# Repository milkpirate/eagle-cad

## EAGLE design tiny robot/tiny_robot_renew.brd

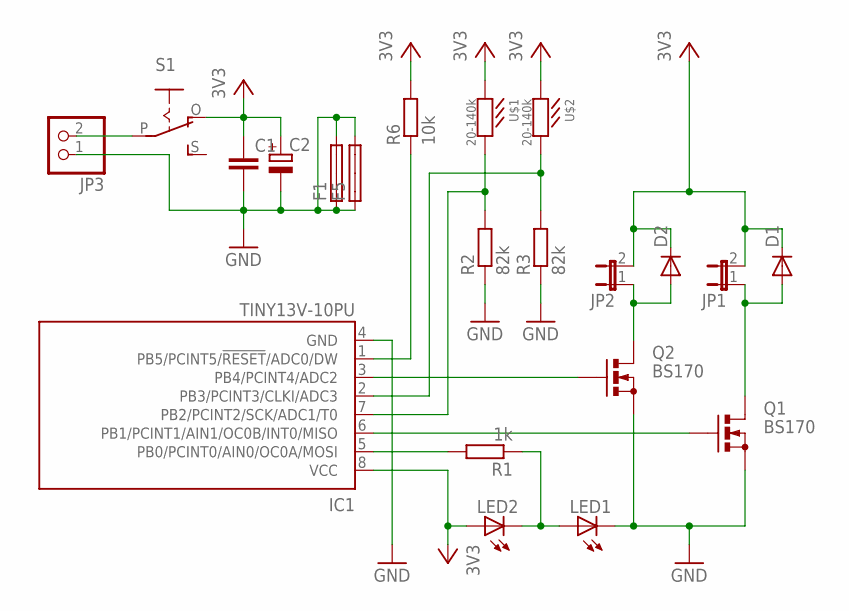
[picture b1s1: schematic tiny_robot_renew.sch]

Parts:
C1: C-EU025-025X050; C025-025X050
C2: CPOL-EUE2,5-6E; E2,5-6E
D1, D2: DIODE-D-2.5; D-2.5
F1: SHK20L
F5: SHK20Q
IC1: TINY13V-10PU; DIL08
JP1, JP2: JP1E; JP1
JP3: PINHD-1X2; 1X02
LED1, LED2: LED3MM
Q1, Q2: BS170; SOT54E
R1: 1k; 0204/7
R2, R3: 82k; 0207/2V
R6: 10k; 0204/7
S1: EG1218S; EG1218
U$1, U$2: 20-140k; LDR-906014

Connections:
GND: C1.2, C2.-, F1.1A, F1.2A, F5.1A, F5.2A, IC1.4 (GND), JP3.1, LED1.K (C), Q1.S, Q2.S, R2.1, R3.1
unnamed: IC1.3 (PB4/PCINT4/ADC2), Q2.G
unnamed: IC1.5 (PB0/PCINT0/AIN0/OC0A/MOSI), R1.2
unnamed: IC1.6 (PB1/PCINT1/AIN1/OC0B/INT0/MISO), Q1.G
unnamed: LED1.A, LED2.K (C), R1.1
unnamed: JP3.2, S1.P
unnamed: D2.A, JP2.1, Q2.D
unnamed: D1.A, JP1.1, Q1.D
unnamed: IC1.2 (PB3/PCINT3/CLKI/ADC3), R3.2, U$2.P$2
unnamed: IC1.7 (PB2/PCINT2/SCK/ADC1/T0), R2.2, U$1.P$2
RST: IC1.1 (PB5/PCINT5/!RESET!/ADC0/DW), R6.1
VCC: C1.1, C2.+, D1.C, D2.C, IC1.8 (VCC), JP1.2, JP2.2, LED2.A, R6.2, S1.O, U$1.P$1, U$2.P$1

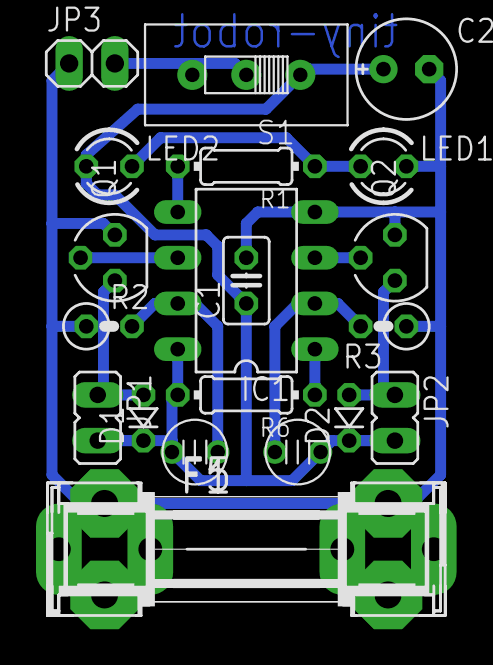
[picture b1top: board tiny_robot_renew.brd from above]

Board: 2 copper layers, 21 parts (0 on the bottom side), 12 nets.

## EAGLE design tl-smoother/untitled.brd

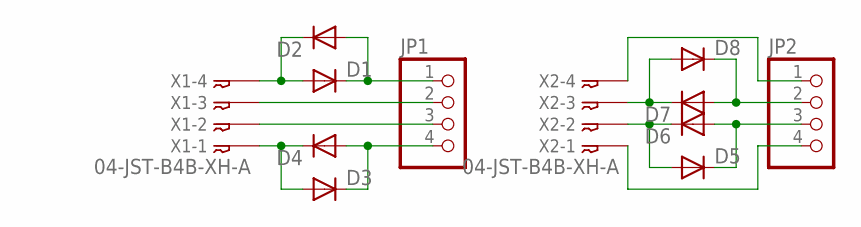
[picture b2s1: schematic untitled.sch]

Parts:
D1, D2, D3, D4: DIODE-SMB; SMB
D5, D6, D7, D8: DIODE-SMC; SMC
JP1, JP2: PINHD-1X4; 1X04
X1, X2: 04-JST-B4B-XH-A; B4B-XH

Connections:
unnamed: JP1.3, X1.P$2
unnamed: JP1.2, X1.P$3
unnamed: D1.C, D2.A, JP1.1
unnamed: D1.A, D2.C, X1.P$4
unnamed: D3.A, D4.C, X1.P$1
unnamed: D3.C, D4.A, JP1.4
unnamed: JP2.4, X2.P$1
unnamed: JP2.1, X2.P$4
unnamed: D7.A, D8.C, JP2.2
unnamed: D7.C, D8.A, X2.P$3
unnamed: D5.A, D6.C, X2.P$2
unnamed: D5.C, D6.A, JP2.3

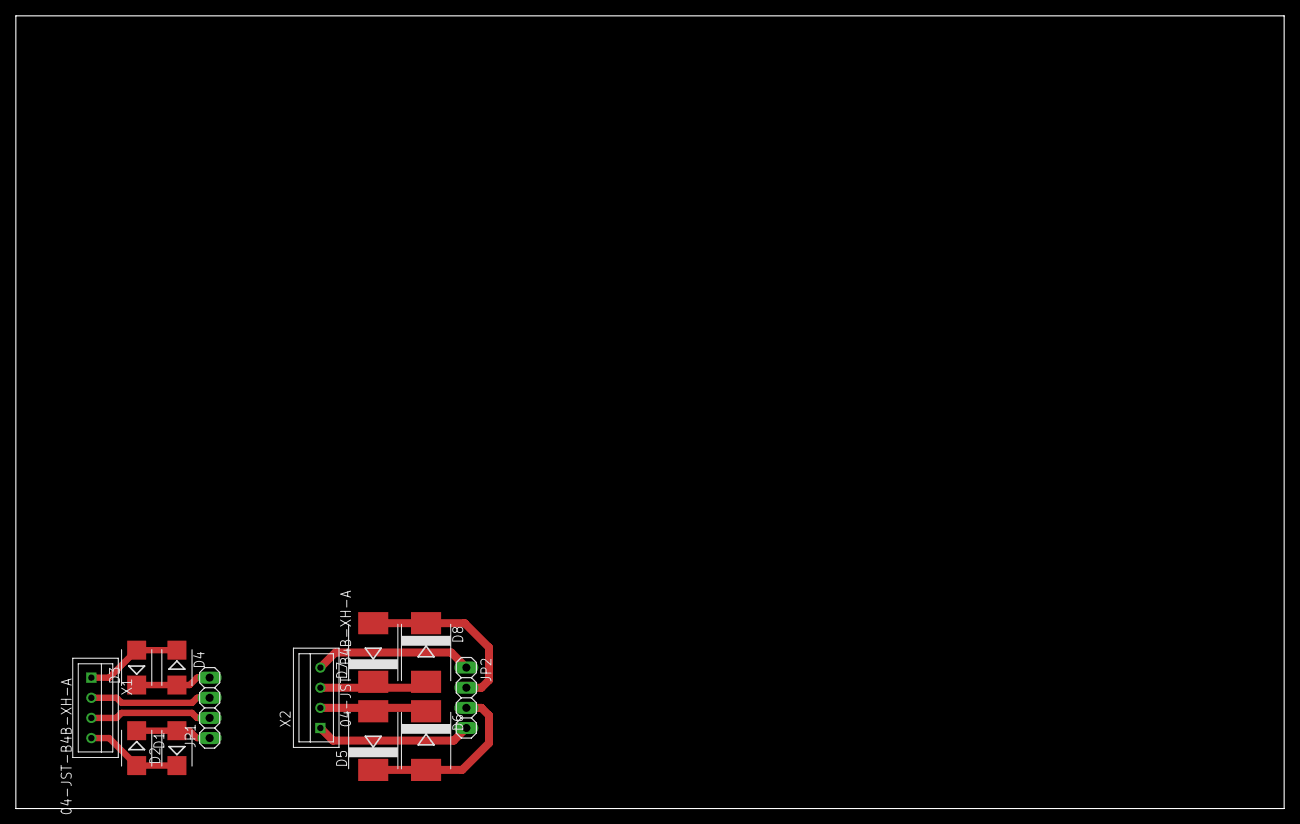
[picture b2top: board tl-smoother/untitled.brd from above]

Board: 2 copper layers, 160.0 x 100.0 mm, 12 parts (0 on the bottom side), 12 nets.

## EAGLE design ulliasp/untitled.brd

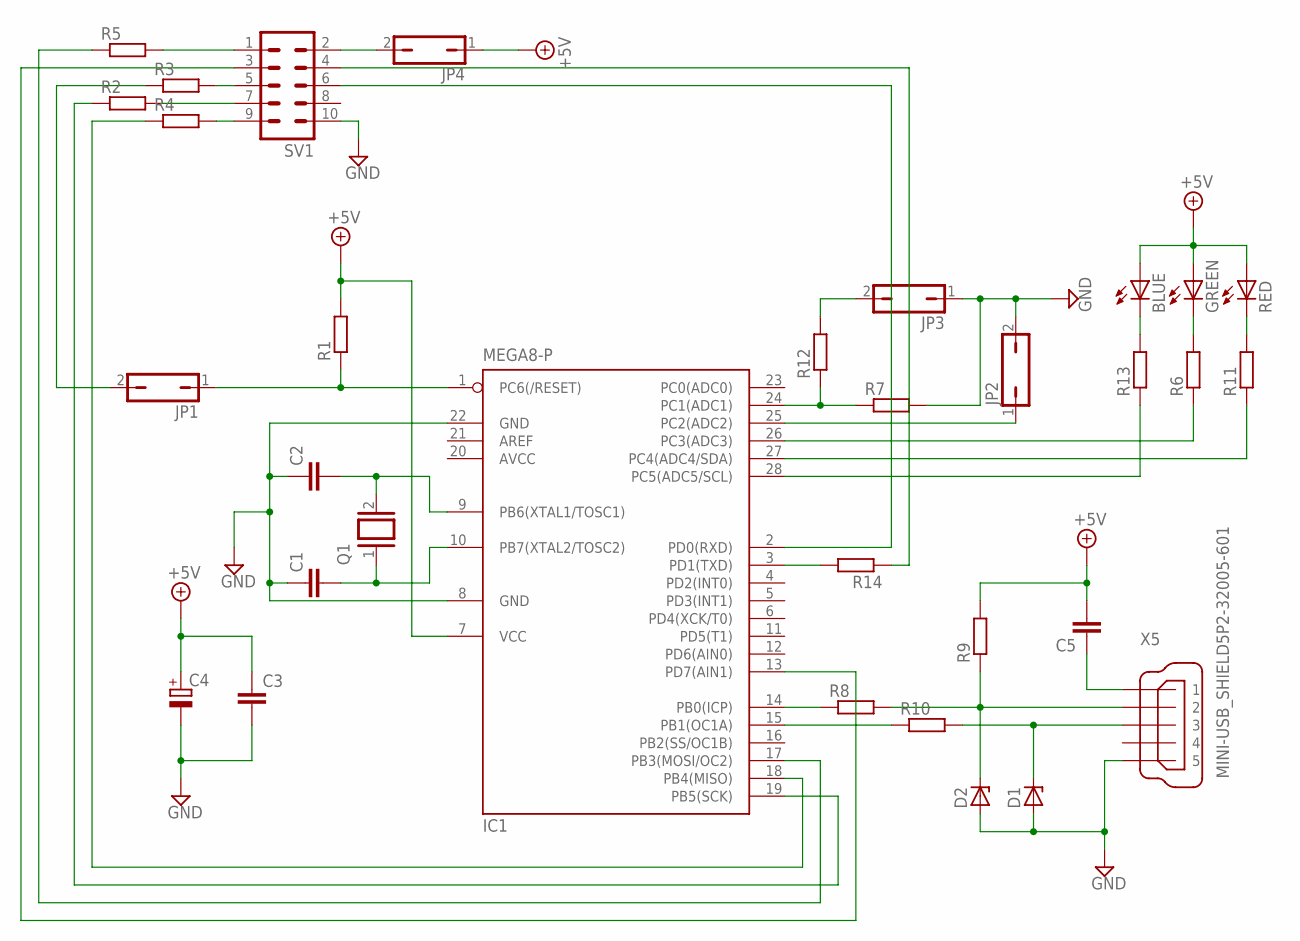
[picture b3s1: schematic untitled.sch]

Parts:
BLUE: LED5MM
C1, C2: C-EU025-025X050; C025-025X050
C3, C5: C-EU025_050-025X075; C025_050-025X075
C4: CPOL-EUE2.5-5; E2,5-5
D1: ZENER-DIODEZD-5; ZDIO-5
D2: ZENER-DIODEZD-2.5; ZDIO-2.5
GREEN: LED5MM
IC1: MEGA8-P; DIL28-3
JP1, JP2, JP3, JP4: JP1Q; JP1
Q1: XTAL/S; QS
R1, R2, R3, R4, R5, R8, R9, R10, R14: R-EU_0207/2V; 0207/2V
R6, R7, R11, R12, R13: R-EU_0204/5; 0204/5
RED: LED5MM
SV1: ML10
X5: MINI-USB_SHIELD5P2-32005-601; 32005-601

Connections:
+5V: BLUE.A, C3.1, C4.+, C5.2, GREEN.A, IC1.7 (VCC), JP4.1, R1.2, R9.2, RED.A
AVCC: IC1.20 (AVCC)
D+: D1.C, R10.2, X5.3
D-: D2.C, R8.2, R9.1, X5.2
GND: C1.1, C2.1, C3.2, C4.-, D1.A, D2.A, IC1.8 (GND), IC1.22 (GND), JP2.2, JP3.1, R7.2, SV1.10, X5.5
MISO: IC1.18 (PB4(MISO)), R4.1
MOSI: IC1.17 (PB3(MOSI/OC2)), R5.1
unnamed: IC1.14 (PB0(ICP)), R8.1
unnamed: IC1.15 (PB1(OC1A)), R10.1
unnamed: IC1.24 (PC1(ADC1)), R7.1, R12.1
unnamed: JP3.2, R12.2
unnamed: IC1.25 (PC2(ADC2)), JP2.1
unnamed: C5.1, X5.1
unnamed: C2.2, IC1.9 (PB6(XTAL1/TOSC1)), Q1.2
unnamed: C1.2, IC1.10 (PB7(XTAL2/TOSC2)), Q1.1
unnamed: IC1.13 (PD7(AIN1)), SV1.3
unnamed: BLUE.K (C), R13.2
unnamed: JP4.2, SV1.2
unnamed: R11.2, RED.K (C)
unnamed: R5.2, SV1.1
unnamed: R3.2, SV1.5
unnamed: R2.2, SV1.7
unnamed: R4.2, SV1.9
unnamed: IC1.3 (PD1(TXD)), R14.2
unnamed: GREEN.K (C), R6.2
unnamed: JP1.2, R3.1
unnamed: IC1.28 (PC5(ADC5/SCL)), R13.1
unnamed: IC1.26 (PC3(ADC3)), R6.1
unnamed: IC1.27 (PC4(ADC4/SDA)), R11.1
RESET: IC1.1 (PC6(/RESET)), JP1.1, R1.1
RX: IC1.2 (PD0(RXD)), SV1.6
SCK: IC1.19 (PB5(SCK)), R2.1
TX: R14.1, SV1.4

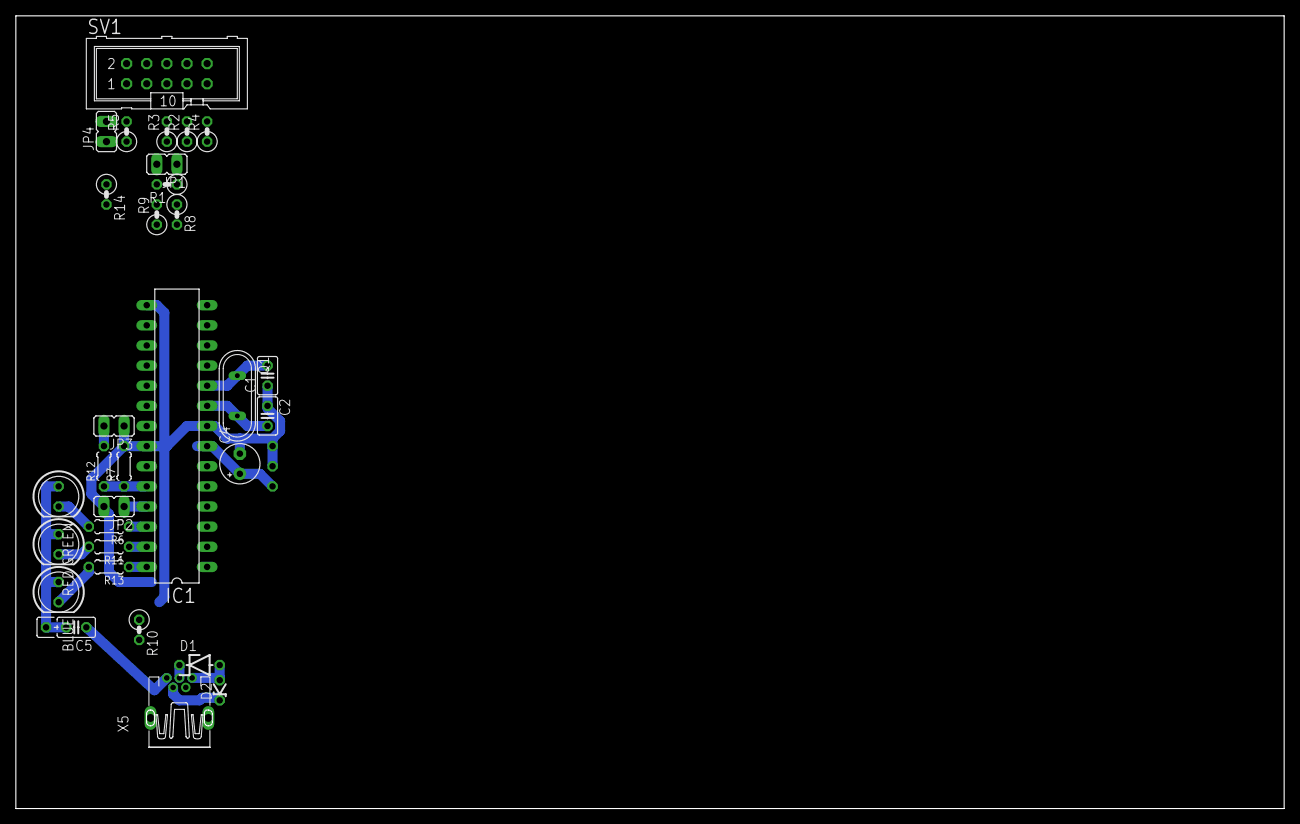
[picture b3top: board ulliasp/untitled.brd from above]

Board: 2 copper layers, 160.0 x 100.0 mm, 32 parts (1 on the bottom side), 32 nets.

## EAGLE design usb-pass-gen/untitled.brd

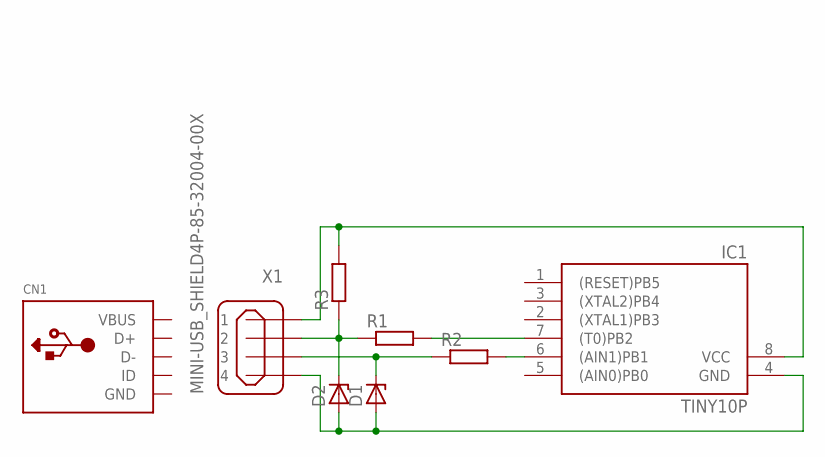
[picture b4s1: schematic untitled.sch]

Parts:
CN1: USBTHM; USB-MINIB-THM
D1: ZENER-DIODEZD-2.5; ZDIO-2.5
D2: ZENER-DIODEZD-5; ZDIO-5
IC1: TINY10P; DIL08
R1, R2, R3: R-EU_0204/2V; 0204V
X1: MINI-USB_SHIELD4P-85-32004-00X; 85-32004-00X

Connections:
GND: CN1.GND
unnamed: IC1.6 ((AIN1)PB1), R2.2
unnamed: IC1.7 ((T0)PB2), R1.2
unnamed: D2.C, R1.1, R3.1, X1.2
unnamed: D1.C, R2.1, X1.3
unnamed: IC1.8 (VCC), R3.2, X1.1
unnamed: D1.A, D2.A, IC1.4 (GND), X1.4
VBUS: CN1.VBUS

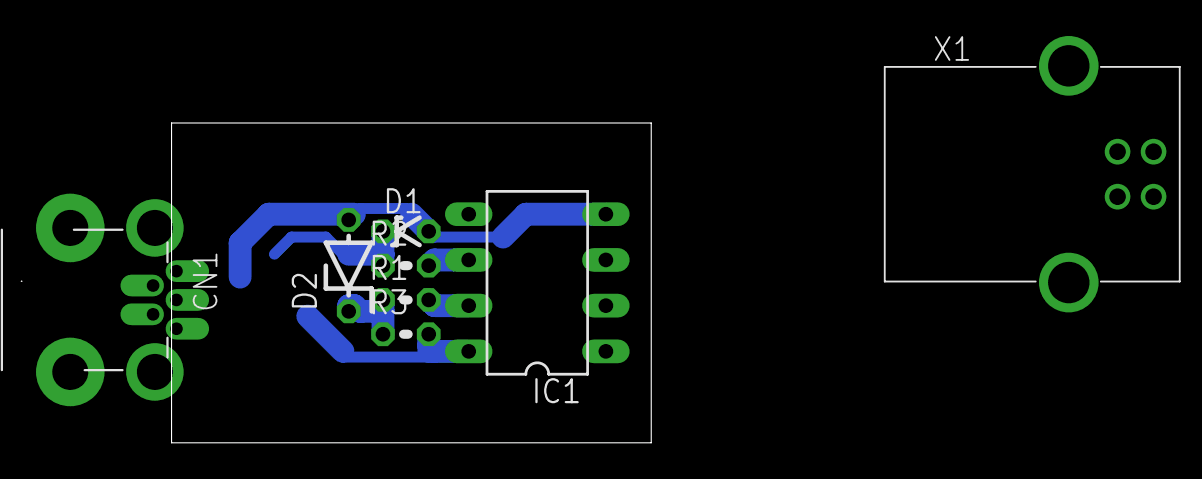
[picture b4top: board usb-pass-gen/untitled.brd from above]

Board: 2 copper layers, 26.7 x 17.8 mm, 8 parts (0 on the bottom side), 6 nets.

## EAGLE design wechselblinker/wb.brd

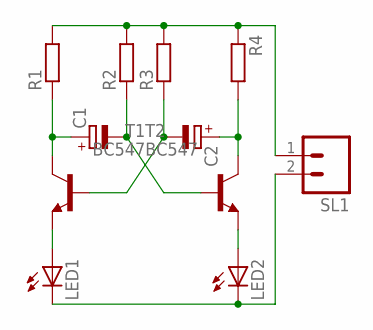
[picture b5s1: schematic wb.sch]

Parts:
C1, C2: CPOL-EUE2.5-7; E2,5-7
LED1, LED2: LED5MM
R1, R2, R3, R4: R-EU_0204/5; 0204/5
SL1: M02; 02P
T1, T2: BC547; TO92

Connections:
GND: LED1.K (C), LED2.K (C), SL1.2
unnamed: C2.-, R3.1, T1.2 (B)
unnamed: C1.-, R2.1, T2.2 (B)
unnamed: C1.+, R1.1, T1.3 (C)
unnamed: C2.+, R4.2, T2.3 (C)
unnamed: LED1.A, T1.1 (E)
unnamed: LED2.A, T2.1 (E)
VCC: R1.2, R2.2, R3.2, R4.1, SL1.1

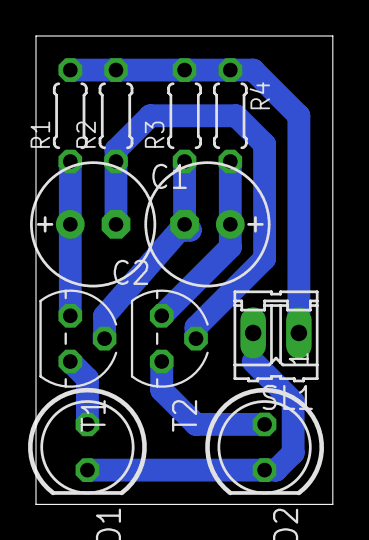
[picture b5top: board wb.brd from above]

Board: 2 copper layers, 16.5 x 26.0 mm, 11 parts (0 on the bottom side), 8 nets.

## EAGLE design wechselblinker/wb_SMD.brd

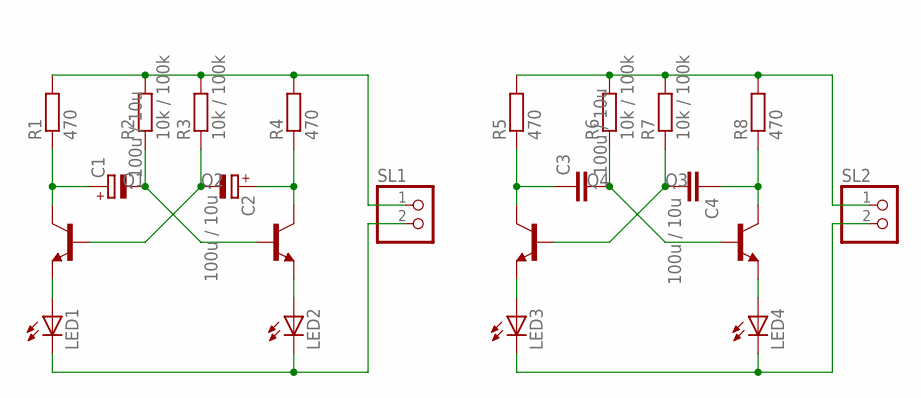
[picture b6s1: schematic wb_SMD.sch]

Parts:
C1, C2: 100u / 10u; PANASONIC_B
C3, C4: 100u / 10u; C0805K
LED1, LED2, LED3, LED4: LEDSML0805; SML0805
Q1, Q2, Q3, Q4: BC817-25-NPN-SOT23-BEC; SOT23-BEC
R1, R4, R5, R8: 470; M1206
R2, R3, R6, R7: 10k / 100k; M1206
SL1, SL2: PINHD-1X2; 1X02

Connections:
GND: LED1.C, LED2.C, SL1.2
GND1: LED3.C, LED4.C, SL2.2
unnamed: C2.-, Q1.B, R3.1
unnamed: C1.-, Q2.B, R2.1
unnamed: C1.+, Q1.C, R1.1
unnamed: C2.+, Q2.C, R4.1
unnamed: LED1.A, Q1.E
unnamed: LED2.A, Q2.E
unnamed: C4.2, Q4.B, R7.1
unnamed: C3.2, Q3.B, R6.1
unnamed: C3.1, Q4.C, R5.1
unnamed: C4.1, Q3.C, R8.1
unnamed: LED3.A, Q4.E
unnamed: LED4.A, Q3.E
VCC: R1.2, R2.2, R3.2, R4.2, SL1.1
VCC1: R5.2, R6.2, R7.2, R8.2, SL2.1

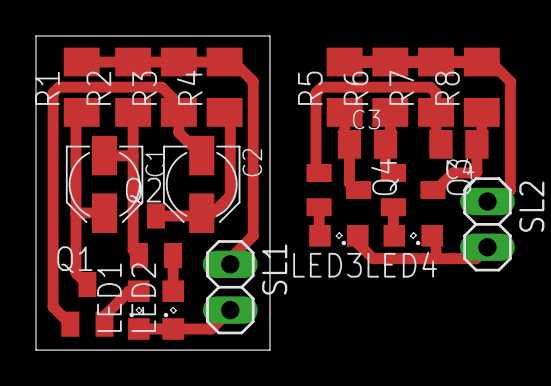
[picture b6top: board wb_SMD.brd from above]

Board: 2 copper layers, 13.0 x 17.4 mm, 22 parts (0 on the bottom side), 16 nets.
